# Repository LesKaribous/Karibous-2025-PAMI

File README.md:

# Project-Template
Template de projet avec documentation

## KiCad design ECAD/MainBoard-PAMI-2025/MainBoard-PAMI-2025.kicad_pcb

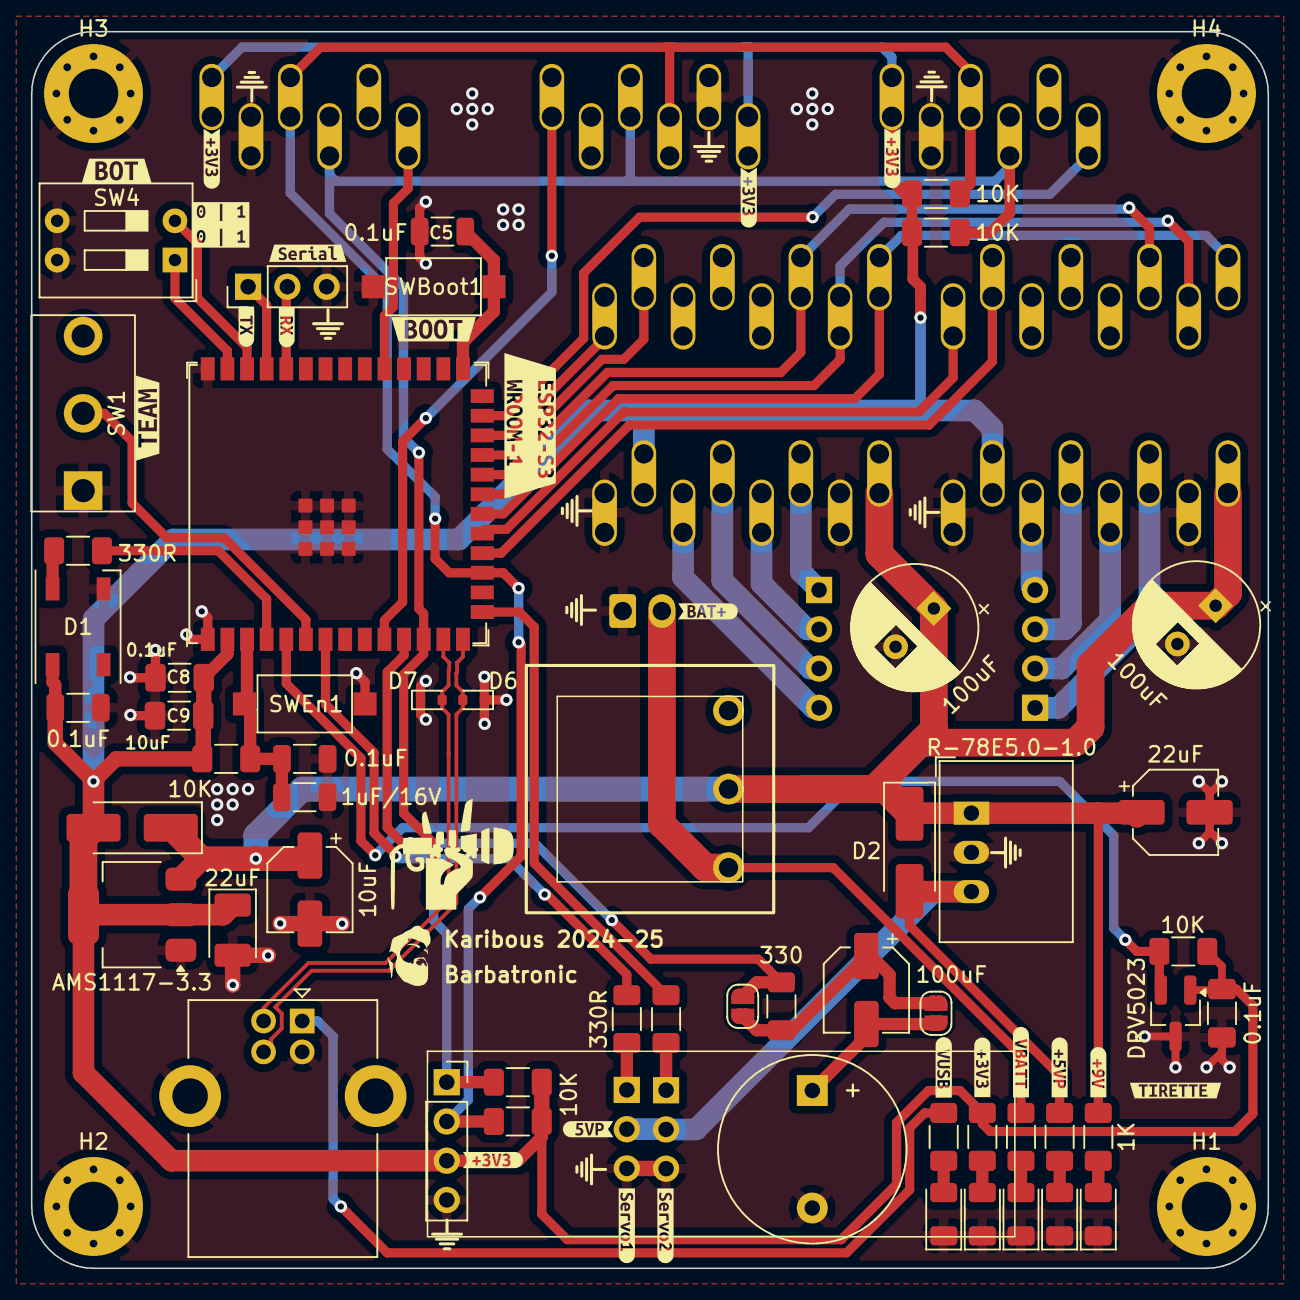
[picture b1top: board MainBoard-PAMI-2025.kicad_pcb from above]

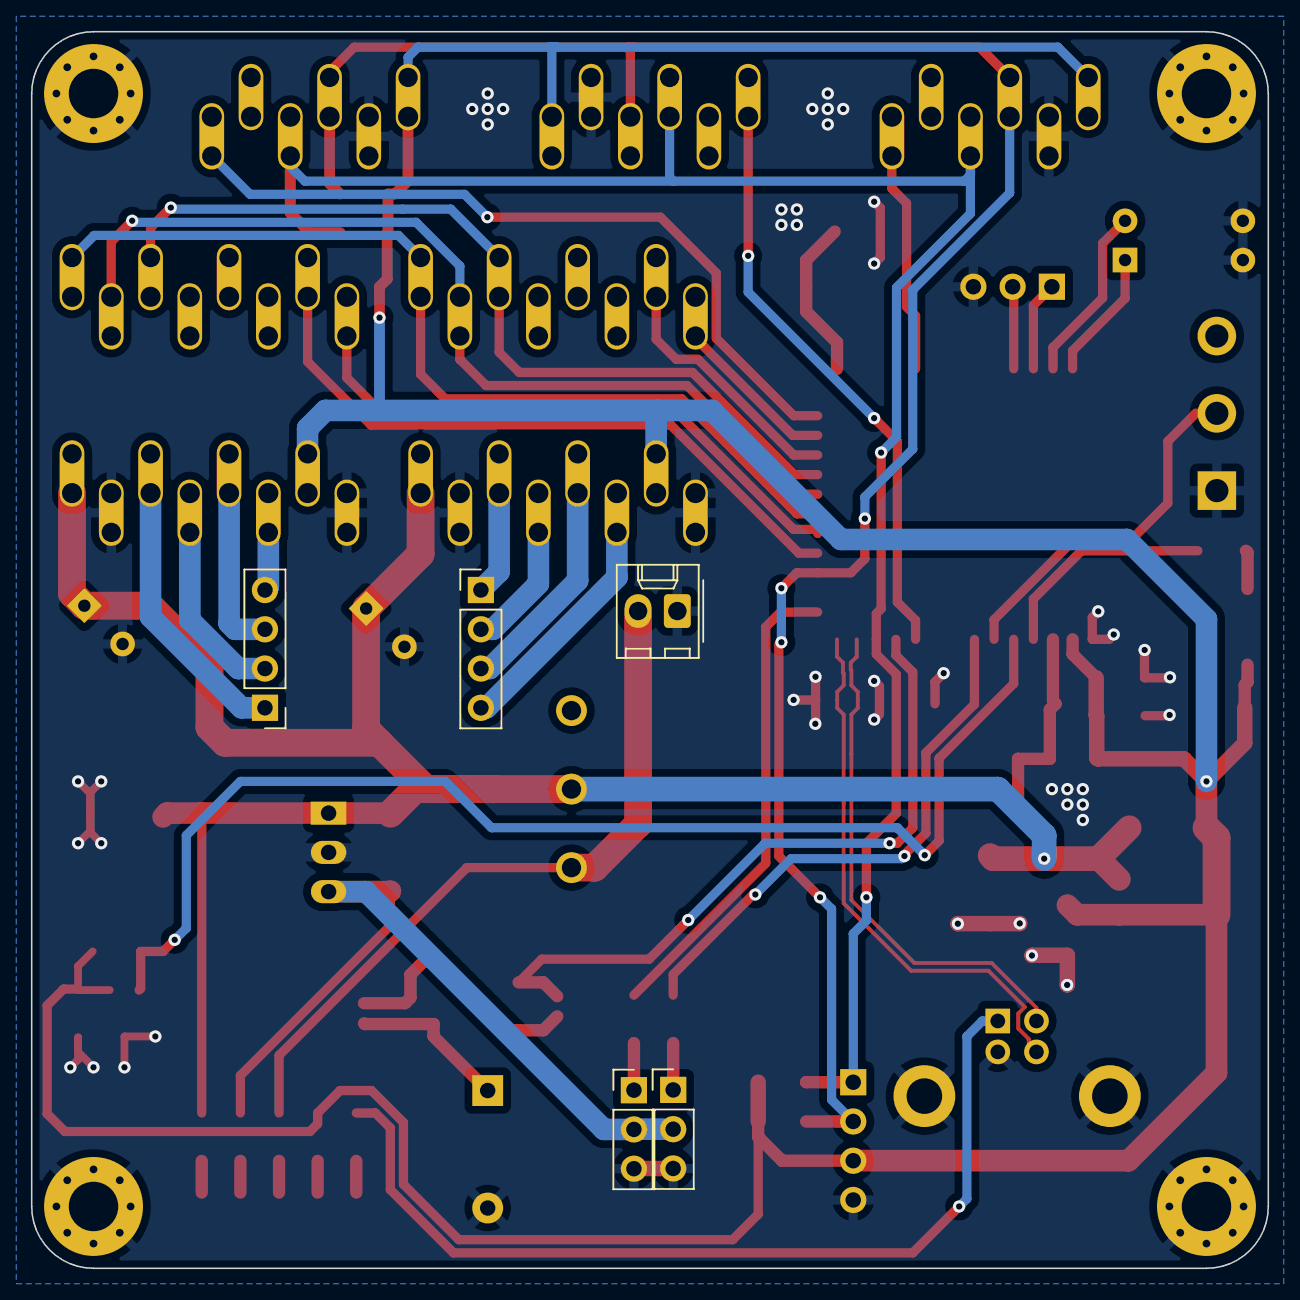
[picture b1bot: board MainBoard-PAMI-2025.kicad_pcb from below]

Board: 2 copper layers, 80.0 x 80.0 mm, 89 parts (8 on the bottom side), 50 nets.

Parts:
BZ2: Buzzer; Buzzer_12x9.5RM7.6
C1: 10uF; CP_Elec_5x5.4
C2: 22uF; CP_EIA-3528-12_Kemet-T_Pad1.50x2.35mm_HandSolder
C3: 1uF/16V; C_1206_3216Metric
C4, C5, C10: 0.1uF; C_1206_3216Metric
C6, C7: 100uF; CP_Radial_D8.0mm_P3.50mm
C8, C13: 0.1uF; C_1206_3216Metric_Pad1.33x1.80mm_HandSolder
C9: 10uF; C_1206_3216Metric_Pad1.33x1.80mm_HandSolder
C11: 22uF; CP_Elec_5x5.4
C12: 100uF; CP_Elec_5x5.4
D1: WS2812B; LED_WS2812B_PLCC4_5.0x5.0mm_P3.2mm
D2, D9: D_Small; D_SMA_Handsoldering
D3: Blue; LED_1206_3216Metric
D4, D8: Red; LED_1206_3216Metric
D5, D10: Green; LED_1206_3216Metric
D6, D7: D_TVS_Bidirectional_Generic; D_SOD-523
H1, H2, H3, H4: MountingHole; MountingHole_3.2mm_M3_Pad_Via
J1: Sensor_Center; VL53 Bottom Entry Version
J2: USB_B; USB_B_Lumberg_2411_02_Horizontal
J3: Sensor_RIGHT; VL53 Bottom Entry Version
J4, J6: Servo; PinHeader_1x03_P2.54mm_Vertical
J5: Sensor_LEFT; VL53 Bottom Entry Version
J7: LeftMotor; PinHeader_1x04_P2.54mm_Vertical
J8: RightMotor; PinHeader_1x04_P2.54mm_Vertical
J10: Serial; PinHeader_1x03_P2.54mm_Vertical
J11: Con_Batt; Molex_KK-254_AE-6410-02A_1x02_P2.54mm_Vertical
J13: OLED; PinSocket_1x04_P2.54mm_Vertical
JP1, JP2: SolderJumper_2_Open; SolderJumper-2_P1.3mm_Open_RoundedPad1.0x1.5mm
R1, R2, R4, R9, R13: 1K; R_1206_3216Metric_Pad1.30x1.75mm_HandSolder
R3, R6, R12: 330R; R_1206_3216Metric_Pad1.30x1.75mm_HandSolder
R5, R7, R8, R10, R11, R15: 10K; R_1206_3216Metric_Pad1.30x1.75mm_HandSolder
R14: 330; R_1206_3216Metric_Pad1.30x1.75mm_HandSolder
SW1: SW_SPDT; SK-12D10 1P2T
SW3: SW_SPDT; UB16SKW03N-C
SW4: SW_DIP_x02; SW_DIP_SPSTx02_Slide_9.78x7.26mm_W7.62mm_P2.54mm
SWBoot1: SW_Boot; SW_SPST_CK_RS282G05A3
SWEn1: SW_EN; SW_SPST_CK_RS282G05A3
U1: ESP32-S3-WROOM-1; ESP32-S3-WROOM-1U
U2: AMS1117-3.3; SOT-223-3_TabPin2
U3, U4: TMC2208_SILENTSTEPSTICK; Step-Stick Driver Bottom Entry Version
U5: R-78E5.0-1.0; Converter_DCDC_RECOM_R-78E-0.5_THT
U6: DRV5023; SOT-23_Handsoldering
kibuzzard-670C04A5, kibuzzard-670C04A5#2, kibuzzard-670C04A5#3, kibuzzard-670C04A5#4: G***; kibuzzard-670C04A5
kibuzzard-670C04EF: G***; kibuzzard-670C04EF
kibuzzard-670C05E9: G***; kibuzzard-670C05E9
kibuzzard-670C07A3: G***; kibuzzard-670C07A3
kibuzzard-670C07E1: G***; kibuzzard-670C07E1
kibuzzard-670C23C9: G***; kibuzzard-670C23C9
kibuzzard-670C045B: G***; kibuzzard-670C045B
kibuzzard-670C047F: G***; kibuzzard-670C047F
kibuzzard-670C057C: G***; kibuzzard-670C057C
kibuzzard-670C058F: G***; kibuzzard-670C058F
kibuzzard-670C060B: G***; kibuzzard-670C060B
kibuzzard-670C061D: G***; kibuzzard-670C061D
kibuzzard-670C077D: G***; kibuzzard-670C077D
kibuzzard-670C0418: G***; kibuzzard-670C0418
kibuzzard-670C0436: G***; kibuzzard-670C0436
kibuzzard-670C0507: G***; kibuzzard-670C0507
kibuzzard-670C0614: G***; kibuzzard-670C0614
kibuzzard-670C0624: G***; kibuzzard-670C0624
kibuzzard-670C0798: G***; kibuzzard-670C0798

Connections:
+3.3V: C2.1, C8.1, C9.1, C10.2, C13.1, D1.1 (VDD), D9.2 (A), J1.1, J3.1, J5.1, J13.3, R4.2, R5.1, R7.1, R8.1, R10.1, R11.1, R15.2, U1.2 (3V3), U2.2 (VO), U3.10 (VIO), U4.10 (VIO), U6.1 (VCC)
+5VP: D2.2 (A), J4.2, J6.2, R13.2, U5.3 (OUT)
+9V: C1.1, C6.1, C7.1, C11.1, D2.1 (K), D9.1 (K), R2.2, SW3.2 (C), U2.3 (VI), U3.16 (VM), U4.16 (VM), U5.1 (IN)
+BATT: J11.2, R9.2, SW3.1 (B)
/D+: D6.2 (A), J2.3 (D+), U1.14 (GPIO20/U1CTS/ADC2_CH9/CLK_OUT1/USB_D+)
/D-: D7.2 (A), J2.2 (D-), U1.13 (GPIO19/U1RTS/ADC2_CH8/CLK_OUT2/USB_D-)
/RX: J10.2, U1.36 (U0RXD/GPIO44/CLK_OUT2)
/TX: J10.1, U1.37 (U0TXD/GPIO43/CLK_OUT1)
Boot_Mode: C5.1, SWBoot1.2, U1.27 (GPIO0/BOOT)
BotNum01: SW4.2, U1.38 (GPIO2/TOUCH2/ADC1_CH1)
BotNum02: SW4.1, U1.39 (GPIO1/TOUCH1/ADC1_CH0)
Buzzer: JP2.2 (B), R14.1, U1.11 (GPIO18/U1RXD/ADC2_CH7/CLK_OUT3)
Chip_PU: C3.1, C4.1, R5.2, SWEn1.2, U1.3 (EN)
Color_Team: SW1.2 (B), U1.6 (GPIO6/TOUCH6/ADC1_CH5)
EnDriver: U1.20 (GPIO12/TOUCH12/ADC2_CH1/FSPICLK/FSPIIO6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), U3.1 (EN), U4.1 (EN)
GND: BZ2.2 (-), C1.2, C2.2, C3.2, C4.2, C5.2, C6.2, C7.2, C8.2, C9.2, C10.1, C11.2, C13.2, D1.3 (VSS), D3.1 (K), D4.1 (K), D5.1 (K), D6.1 (K), D7.1 (K), D8.1 (K), D10.1 (K), H1.1, H2.1, H3.1, H4.1, J1.2, J2.4 (GND), J2.5 (Shield), J3.2, J4.3, J5.2, J6.3, J10.3, J11.1, J13.4, SW1.1 (A), SW4.3, SW4.4, SWBoot1.1, SWEn1.1, U1.1 (GND), U1.40 (GND), U1.41 (GND), U2.1 (GND), U3.9 (GND), U3.15 (GND), U4.9 (GND), U4.15 (GND), U5.2 (GND), U6.3 (GND)
LED_Status: R3.2, U1.4 (GPIO4/TOUCH4/ADC1_CH3)
LeftDir: U1.24 (GPIO47/SPICLK_P/SUBSPICLK_P_DIFF), U4.8 (DIR)
LeftMS1: U1.21 (GPIO13/TOUCH13/ADC2_CH2/FSPIQ/FSPIIO7/S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), U3.2 (MS1), U4.2 (MS1)
LeftMS2: U1.22 (GPIO14/TOUCH14/ADC2_CH3/FSPIWP/FSPIDQS/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), U3.3 (MS2), U4.3 (MS2)
LeftStep: U1.23 (GPIO21), U4.7 (STEP)
unnamed: BZ2.1 (+), C12.2, JP1.1 (A)
unnamed: D1.4 (DIN), R3.1
unnamed: D3.2 (A), R1.1
unnamed: D4.2 (A), R2.1
unnamed: D5.2 (A), R4.1
unnamed: D8.2 (A), R9.1
unnamed: D10.2 (A), R13.1
unnamed: J2.1 (VBUS), R1.2
unnamed: J4.1, R6.2
unnamed: J6.1, R12.2
unnamed: J7.1, U4.14 (OA2)
unnamed: J7.2, U4.13 (OA1)
unnamed: J7.3, U4.12 (OB1)
unnamed: J7.4, U4.11 (OB2)
unnamed: J8.1, U3.14 (OA2)
unnamed: J8.2, U3.13 (OA1)
unnamed: J8.3, U3.12 (OB1)
unnamed: J8.4, U3.11 (OB2)
unnamed: C12.1, JP1.2 (B), JP2.1 (A), R14.2
RightDir: U1.19 (GPIO11/TOUCH11/ADC2_CH0/FSPID/FSPIIO5/S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), U3.8 (DIR)
RightStep: U1.18 (GPIO10/TOUCH10/ADC1_CH9/FSPICS0/FSPIIO4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), U3.7 (STEP)
SCL: J1.3, J3.3, J5.3, J13.2, R7.2, R10.2, U1.17 (GPIO9/TOUCH9/ADC1_CH8/FSPIHD/SUBSPIHD)
SDA: J1.4, J3.4, J5.4, J13.1, R8.2, R11.2, U1.12 (GPIO8/TOUCH8/ADC1_CH7/SUBSPICS1)
Servo01: R6.1, U1.7 (GPIO7/TOUCH7/ADC1_CH6)
Servo02: R12.1, U1.15 (GPIO3/TOUCH3/ADC1_CH2)
Tirette: R15.1, U1.5 (GPIO5/TOUCH5/ADC1_CH4), U6.2 (OUT)
XSHUT_CENTER: J1.6, U1.10 (GPIO17/U1TXD/ADC2_CH6)
XSHUT_LEFT: J5.6, U1.31 (GPIO38/FSPIWP/SUBSPIWP)
XSHUT_RIGHT: J3.6, U1.25 (GPIO48/SPICLK_N/SUBSPICLK_N_DIFF)

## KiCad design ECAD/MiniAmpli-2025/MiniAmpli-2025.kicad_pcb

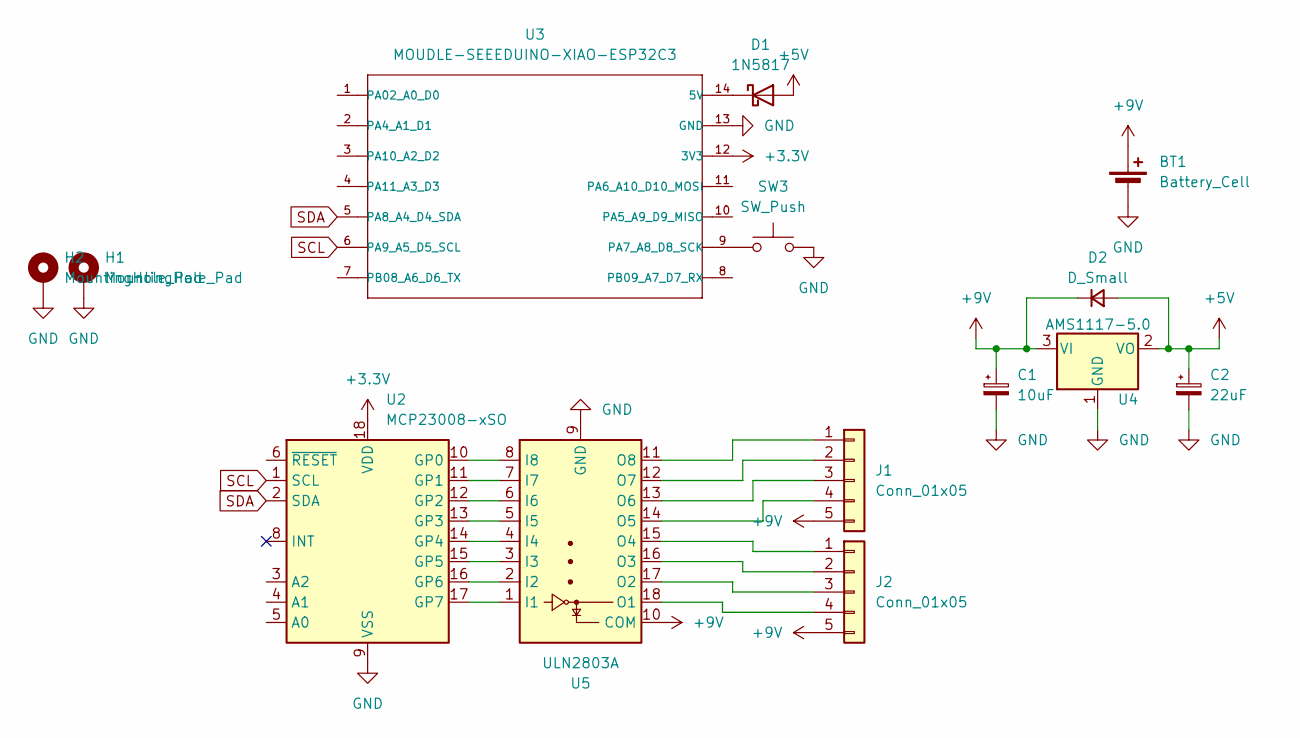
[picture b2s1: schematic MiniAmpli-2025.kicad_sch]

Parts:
BT1: Battery_Cell; BatteryHolder_Eagle_12BH611-GR
C1: 10uF; CP_Elec_5x5.4
C2: 22uF; CP_EIA-3528-12_Kemet-T_Pad1.50x2.35mm_HandSolder
D1: 1N5817; D_DO-41_SOD81_P7.62mm_Horizontal
D2: D_Small; D_SMA_Handsoldering
H1, H2: MountingHole_Pad; MountingHole_3.2mm_M3_Pad_Via
J1, J2: Conn_01x05; JST_XH_B5B-XH-A_1x05_P2.50mm_Vertical
SW3: SW_Push; SW_XKB_DM1-16UP-1
U2: MCP23008-xSO; SOIC-18W_7.5x11.6mm_P1.27mm
U3: MOUDLE-SEEEDUINO-XIAO-ESP32C3; MOUDLE14P-SMD-2.54-21X17.8MM
U4: AMS1117-5.0; SOT-223-3_TabPin2
U5: ULN2803A; SOIC-18W_7.5x11.6mm_P1.27mm

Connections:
+3.3V: U2.18 (VDD), U3.12 (3V3)
+5V: C2.1, D1.2 (A), D2.2 (A), U4.2 (VO)
+9V: BT1.1 (+), C1.1, D2.1 (K), J1.5, J2.5, U4.3 (VI), U5.10 (COM)
GND: BT1.2 (-), C1.2, C2.2, H1.1, H2.1, SW3.2, U2.9 (VSS), U3.13 (GND), U4.1 (GND), U5.9 (GND)
unnamed: D1.1 (K), U3.14 (5V)
unnamed: J1.1, U5.11 (O8)
unnamed: J1.2, U5.12 (O7)
unnamed: J1.3, U5.13 (O6)
unnamed: J1.4, U5.14 (O5)
unnamed: J2.1, U5.15 (O4)
unnamed: J2.2, U5.16 (O3)
unnamed: J2.3, U5.17 (O2)
unnamed: J2.4, U5.18 (O1)
unnamed: U2.10 (GP0), U5.8 (I8)
unnamed: U2.11 (GP1), U5.7 (I7)
unnamed: U2.12 (GP2), U5.6 (I6)
unnamed: U2.13 (GP3), U5.5 (I5)
unnamed: U2.14 (GP4), U5.4 (I4)
unnamed: U2.15 (GP5), U5.3 (I3)
unnamed: U2.16 (GP6), U5.2 (I2)
unnamed: U2.17 (GP7), U5.1 (I1)
unnamed: SW3.1, U3.9 (PA7_A8_D8_SCK)
SCL: U2.1 (SCL), U3.6 (PA9_A5_D5_SCL)
SDA: U2.2 (SDA), U3.5 (PA8_A4_D4_SDA)

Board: 2 copper layers, 14 parts (3 on the bottom side), 24 nets, no tracks yet.

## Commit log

2024-06-01 NewBoard 2025
2024-06-01 update PCB
2024-06-01 Everything that need to be here :)
2024-06-01 Quick routing
2024-06-02 Clean repo
2024-06-02 Optimize routing
2024-09-30 Change switch + regulator + Servo Power
2024-10-11 add sensor center
2024-10-11 new sensor position - new PCB size
2024-10-11 first prototype
2024-10-12 Update Live 206
    Update Battery
    Add Recom 5V
    Add ASM1117
    Add capacitor
    Change sensor header
    Move components
2024-10-13 Add buzzer
2024-10-13 routage + silkscreen
2024-10-13 Change for DRV5023 - New 3D
2024-10-13 New halle effect sensor for tirette
2024-11-02 WIP PAMI 2025
2024-11-03 new carter, arm and side support
2024-11-04 backup
2024-11-04 export for CNC
2024-11-04 Add plan for laser
2024-11-04 fix holes for servomotors
2024-11-05 add bom
2024-11-16 new code for 2025
2024-11-16 quick save
2024-11-16 quick name fix
2024-11-16 change PCB position / carter
2024-11-19 Add diffuseur and BAU
2024-11-21 fix sensor - Test sensor and tirette
2024-11-23 Live 210 - Modif Roue, Bride connecteur et tirette
2024-11-25 modify carter
2024-11-25 test slope (PAMI 0)
2024-11-27 update tirette and carter
2024-11-27 fix serial monitoring issue
2024-11-27 activate detection
2024-11-27 datum and strategy for Superstar (Yellow)
2024-11-28 Optimize time | Fiesta mode and actuators new values
2024-11-28 add new arm and modify BAU
2024-11-28 backups
2024-11-28 Introducing Fiesta ! 🎉🎉
2024-11-28 remove fiesta test
2024-11-29 Update 3D print files
2024-12-02 update second arm
2024-12-02 3D export for website
2024-12-30 backup Kicad
2025-01-28 Correct paths for case-sensitive filesystems
2025-01-29 Nex PCB Mini Pami
2025-01-29 minor update
2025-02-23 New diffus
2025-02-26 new carter and spacer
2025-02-28 add holes for arms
2025-03-02 mini ampli
2025-03-02 tirette
2025-03-04 init ok for all PAMI / Color
2025-03-04 add info LCD at the end of the match
2025-03-04 improve end match if opponent detected
    Le robot saute maintenant à la fin de match même si il détecte un robot adverse et reste bloqué
2025-03-04 Superstar Match is Ready 🎉🎉
2025-03-05 implemented pause
2025-03-05 implement match for groupies
2025-03-14 Moustache
2025-03-14 add gridfinity boxes
2025-03-15 Add Moustache03
2025-04-18 update match time and delay
2025-04-21 stable belgium 2025
2025-04-25 live 225 - add support for sensors and debug
2025-05-17 WIP -> TODO : Change distanceToGo to Accel and distance
2025-05-18 WIP - Synchro actuators and sensors filtering
2025-05-18 WIP - New melody asynchronous
2025-05-26 Before CDR
2025-06-07 sensor filter - WIP
2025-06-07 Strat CDR 2025
2026-01-13 New pcb - Ninja SIMA
